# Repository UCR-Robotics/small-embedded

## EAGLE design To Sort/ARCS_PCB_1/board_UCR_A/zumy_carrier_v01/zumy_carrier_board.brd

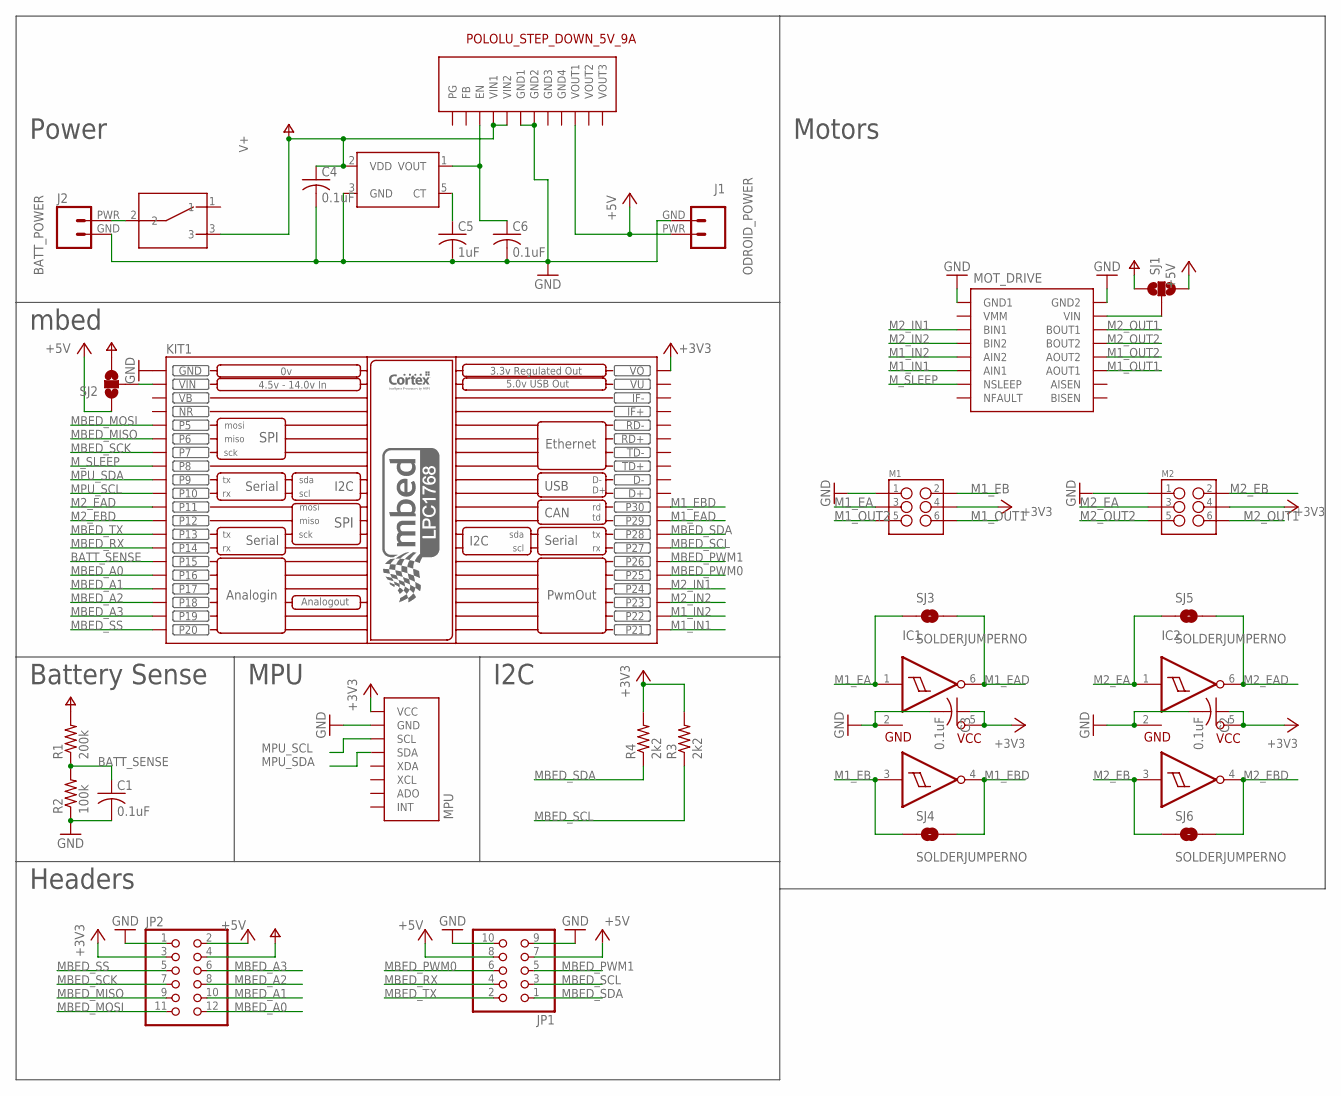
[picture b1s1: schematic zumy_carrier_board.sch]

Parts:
C1, C2, C3, C4, C6: 0.1uF; C1206
C5: 1uF; C1206
IC1, IC2: SN74AUP2G17; SC-70-6
J1: ODROID_POWER; ODOIRD_PWR
J2: BATT_POWER
JP1: PINHD-2X5; 2X05
JP2: PINHD-2X6; 2X06
KIT1: MBED_NXP_LPC1768; MBED-KIT
M1, M2: M03X2SHROUD; 2X3-SHROUDED
MOT_DRIVE: POLOLU_DRV8833_MODULE
MPU: ITG/MPU_MODULE
R1: 200k; R1206
R2: 100k; R1206
R3, R4: 2k2; R1206
SJ1, SJ2: SOLDERJUMPER_2WAYT; SJ_2
SJ3, SJ4, SJ5, SJ6: SOLDERJUMPERNO; SJ_2S-NO
SW1: 500SSP1S1M6QEA; 500SSP1S1M6QEA_SWITCH
U$2: BD5260G; SOT23-5
U$3: POLOLU_STEP_DOWN_5V_9A

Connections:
+3V3: C2.1, C3.1, IC1.5 (VCC), IC2.5 (VCC), JP2.3, KIT1.VOUT (VO), M1.4, M2.4, MPU.VCC, R3.2, R4.2
+5V: J1.PWR, JP1.7, JP1.8, JP2.2, SJ1.3, SJ2.1, U$3.VOUT1
BATT_SENSE: C1.1, KIT1.P$15 (P15), R1.1, R2.2
GND: C1.2, C2.2, C3.2, C4.2, C5.2, C6.2, IC1.2 (GND), IC2.2 (GND), J1.GND, J2.GND, JP1.9, JP1.10, JP2.1, KIT1.GND, M1.1, M2.1, MOT_DRIVE.GND1, MOT_DRIVE.GND2, MPU.GND, R2.1, U$2.3 (GND), U$3.GND1, U$3.GND2
M1_EA: IC1.1 (1A), M1.3, SJ3.1
M1_EAD: IC1.6 (1Y), KIT1.P$29 (P29), SJ3.2
M1_EB: IC1.3 (2A), M1.2, SJ4.1
M1_EBD: IC1.4 (2Y), KIT1.P$30 (P30), SJ4.2
M1_IN1: KIT1.P$21 (P21), MOT_DRIVE.AIN1
M1_IN2: KIT1.P$22 (P22), MOT_DRIVE.AIN2
M1_OUT1: M1.6, MOT_DRIVE.AOUT1
M1_OUT2: M1.5, MOT_DRIVE.AOUT2
M2_EA: IC2.1 (1A), M2.3, SJ5.1
M2_EAD: IC2.6 (1Y), KIT1.P$11 (P11), SJ5.2
M2_EB: IC2.3 (2A), M2.2, SJ6.1
M2_EBD: IC2.4 (2Y), KIT1.P$12 (P12), SJ6.2
M2_IN1: KIT1.P$24 (P24), MOT_DRIVE.BIN1
M2_IN2: KIT1.P$23 (P23), MOT_DRIVE.BIN2
M2_OUT1: M2.6, MOT_DRIVE.BOUT1
M2_OUT2: M2.5, MOT_DRIVE.BOUT2
MBED_A0: JP2.12, KIT1.P$16 (P16)
MBED_A1: JP2.10, KIT1.P$17 (P17)
MBED_A2: JP2.8, KIT1.P$18 (P18)
MBED_A3: JP2.6, KIT1.P$19 (P19)
MBED_MISO: JP2.9, KIT1.P$6 (P6)
MBED_MOSI: JP2.11, KIT1.P$5 (P5)
MBED_PWM0: JP1.6, KIT1.P$25 (P25)
MBED_PWM1: JP1.5, KIT1.P$26 (P26)
MBED_RX: JP1.4, KIT1.P$14 (P14)
MBED_SCK: JP2.7, KIT1.P$7 (P7)
MBED_SCL: JP1.3, KIT1.P$27 (P27), R3.1
MBED_SDA: JP1.1, KIT1.P$28 (P28), R4.1
MBED_SS: JP2.5, KIT1.P$20 (P20)
MBED_TX: JP1.2, KIT1.P$13 (P13)
MPU_SCL: KIT1.P$10 (P10), MPU.SCL
MPU_SDA: KIT1.P$9 (P9), MPU.SDA
M_SLEEP: KIT1.P$8 (P8), MOT_DRIVE.NSLEEP
unnamed: KIT1.VIN, SJ2.2
unnamed: J2.PWR, SW1.2
unnamed: MOT_DRIVE.VIN, SJ1.2
unnamed: C6.1, U$2.1 (VOUT), U$3.EN
unnamed: C5.1, U$2.5 (CT)
NR: KIT1.NR
V+: C4.1, JP2.4, R1.2, SJ1.1, SJ2.3, SW1.3, U$2.2 (VDD), U$3.VIN1, U$3.VIN2
VB: KIT1.VB
VU: KIT1.VU

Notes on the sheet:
Motors
Power
mbed
MPU
I2C
Headers
Battery Sense

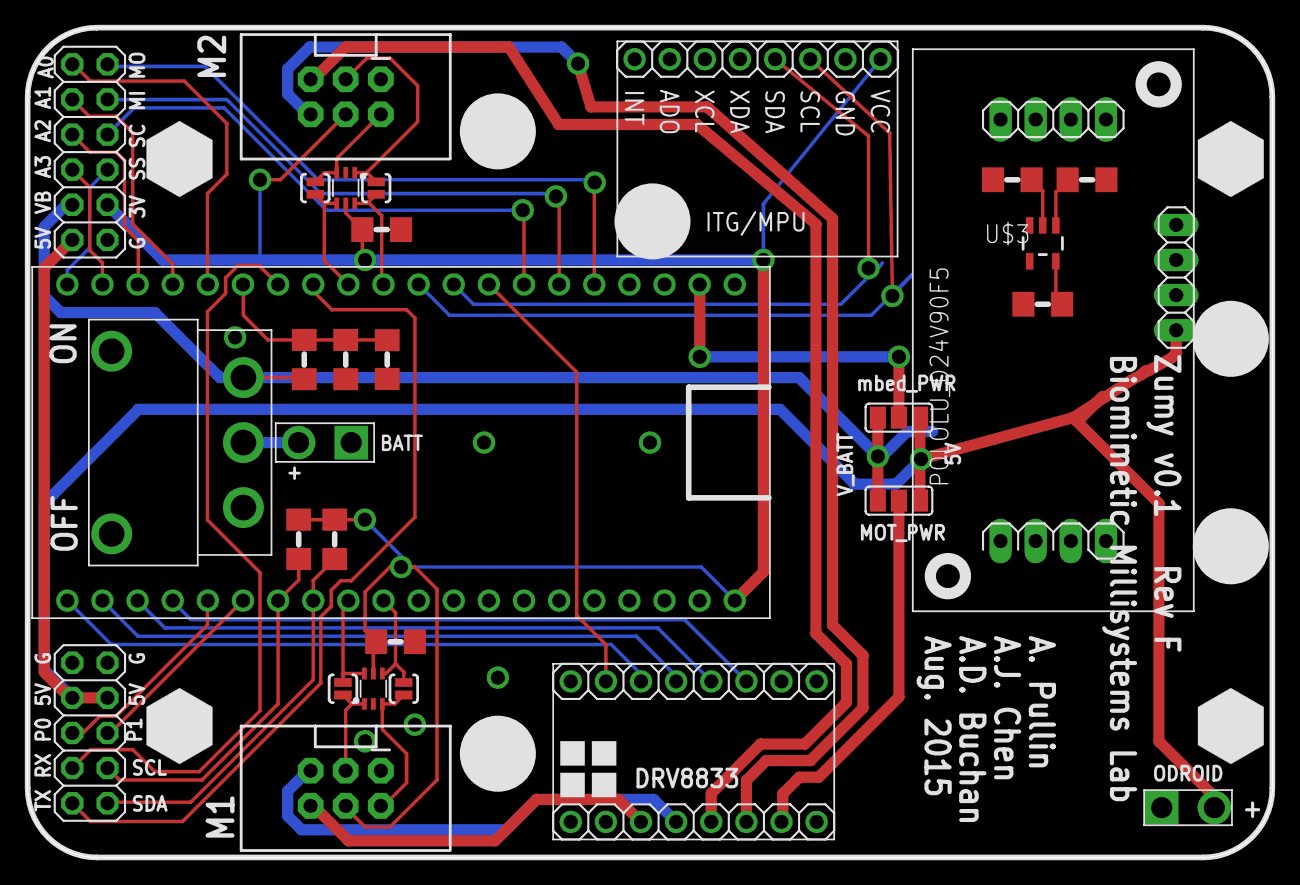
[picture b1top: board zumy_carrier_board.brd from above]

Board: 2 copper layers, 90.0 x 60.0 mm, 32 parts (0 on the bottom side), 43 nets.

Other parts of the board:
U$1: CHASSIS_STANDOFF
U$4: STANDOFF_POSITION

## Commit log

2018-04-08 init repo, copied ucb board files
2018-04-28 modifying PCB to update voltage regulator
2018-05-06 reorganized some folders
2018-05-31 ARCS Library update
2018-07-11 major additions to arcs-ecu-rev1
2018-07-11 organized folders

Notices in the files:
parts and their libraries:
SparkFun-Connectors: Licensing: Creative Commons ShareAlike 4.0 International - https://creativecommons.org/licenses/by-sa/4.0
SparkFun-Passives: Licensing: CC v3.0 Share-Alike You are welcome to use this library for commercial purposes.
biomimetic: UC Regents. All rights reserved.
